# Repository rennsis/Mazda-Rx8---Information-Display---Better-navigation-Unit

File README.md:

In this project i want to share my work for the Mazda RX8 information diplay and the parts that connected to it.

I started the project while working on a "remake" for the navigation unit. Basiclly i want to replace the OEM Navigation unit with an own programmed display where u can see sensors and also troubleshoot your car for example a DTC read out.

Some information in the project i got from already dead github projects. So i will try to continue there work :) Also i alredy want to say thanks to these poeple who was able to help me with there information! 

Currently there wont be much in this Project cause im currently planing on desinging a PCB where everthing will connect. 

| ICON | DATA | ADDRESS |
| ------------- | ------------- | ------------- |
| CD-IN | 0x10 | 0x93 |
| MD-IN | 0x10 | 0x94 |
| L-DIVIDER | 0x10 | 0x91 |
| R-DIVIDER | 0x08 | 0x9B |
| ST | 0x10 | 0x95 |
| DA | 0x01 | 0x95 |
| C° | 0x10 | 0x96 |
| F° | 0x08 | 0x96 |
| TEMP | 0x04 | 0x96 |
| AMB | 0x02 | 0x96 |
| AF | 0x01 | 0x96 |
| CAR | 0x01 | 0x97 |
| PTY | 0x02 | 0x97 |
|  AIR-IN | 0x04 | 0x97 |
| AIR-REUSE | 0x08 | 0x97 |
| AUTO | 0x10 | 0x97 |
| FAN | 0x02 | 0x99 |
| FAN-1 | 0x04 | 0x99 |
| FAN-2 | 0x08 | 0x99 |
| FAN-3 | 0x10 | 0x99 |
| FAN-4 | 0x01 | 0x98 |
| FAN-5 | 0x04 | 0x98 |
| FAN-6 | 0x08 | 0x9D |
| FAN-7 | 0x02 | 0x9B |
| RPT | 0x20 | 0x98 |
| AC | 0x08 | 0x98 |
| ECO | 0x10 | 0x98 |
| AUTO-M | 0x01 | 0x9A |
| TP | 0x02 | 0x9A |
| TA | 0x04 | 0x9A |
| RDM | 0x08 | 0x9A |
| TEXT " | 0x04 | 0x9B |
| TEXT : | 0x10 | 0x9D |
| TEXT-R . | 0x10 | 0x9B |
| PERSON | 0x01 | 0x9C |
| FRONT-HEAT | 0x02 | 0x9C |
| ARROW-FEED | 0x04 | 0x9C |
| ARROW-FACE | 0x04 | 0x9D |
| TMP . | 0x02 | 0x9D |
| CLOCK : | 0x04 | 0x93 |
| CLOCK . | 0x04 | 0x90 |

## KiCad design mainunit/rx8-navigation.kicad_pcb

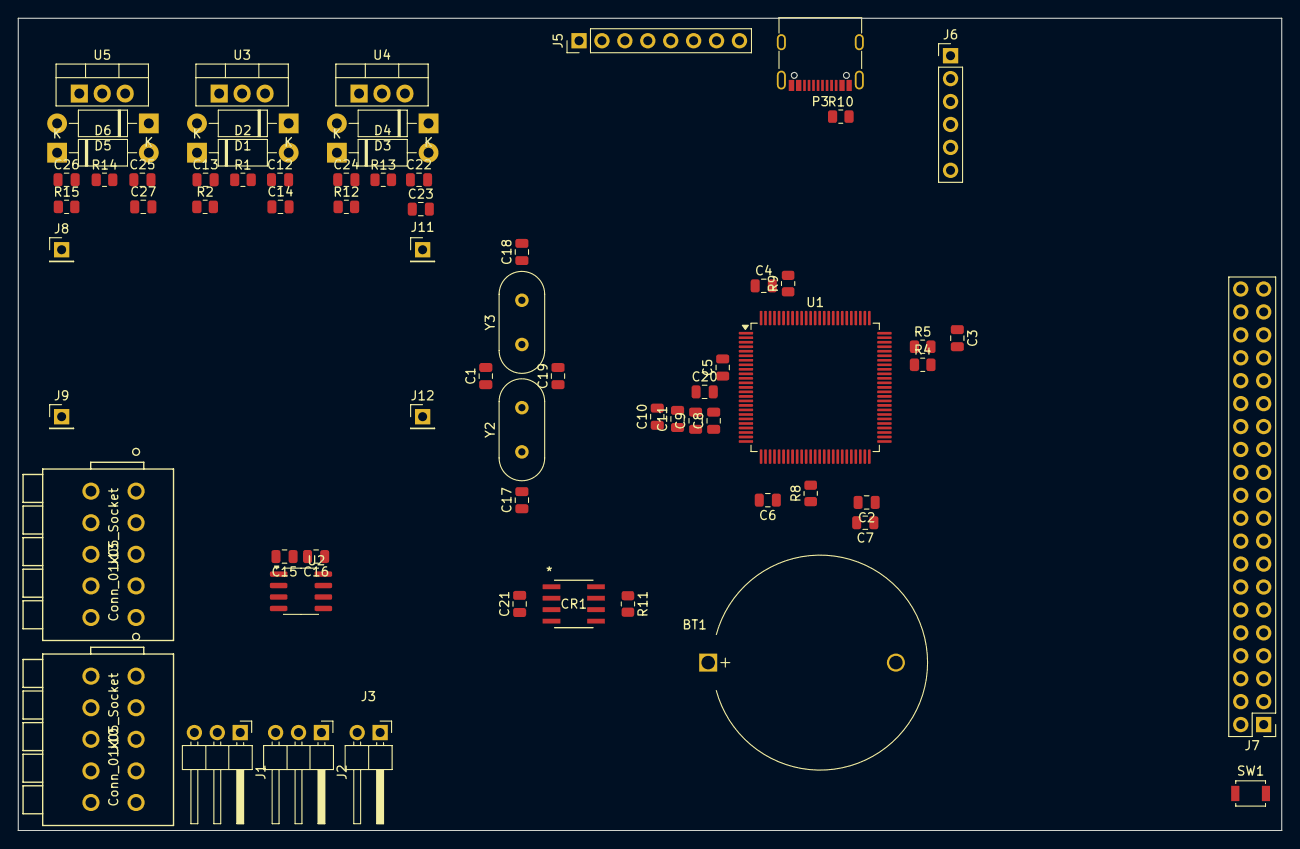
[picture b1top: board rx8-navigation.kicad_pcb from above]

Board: 4 copper layers, 140.0 x 90.0 mm, 68 parts (0 on the bottom side), 62 nets, no tracks yet.

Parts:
BT1: Battery_Cell; BatteryHolder_MYOUNG_BS-07-A1BJ001_CR2032
C1, C17: 10pF; C_SMD
C2, C3, C4, C5, C6, C15, C16, C21: 100nF; C_SMD
C7: 4.7uF; C_SMD
C8, C10: 10nF; C_SMD
C9, C11, C14, C23, C27: 1uF; C_SMD
C12, C20, C22, C25: 0.1uF; C_SMD
C13, C24, C26: 10uF; C_SMD
C18, C19: 20pF; C_SMD
CR1: L9616; SO-8_STM
D1, D2, D3, D4, D5, D6: 1N4001; D_DO-41_SOD81_P10.16mm_Horizontal
J1: BOOT1; PinHeader_1x03_P2.54mm_Horizontal
J2: BOOT0; PinHeader_1x03_P2.54mm_Horizontal
J3: RX/TX; PinHeader_1x02_P2.54mm_Horizontal
J5: MPU-69050; PinHeader_1x08_P2.54mm_Vertical
J6: HC-06; PinHeader_1x06_P2.54mm_Vertical
J7: TFT_Unit; PinHeader_2x20_P2.54mm_Vertical
J8: RegV_IN+; PinHeader_1x01_P2.54mm_Vertical
J9: RegV_IN-; PinHeader_1x01_P2.54mm_Vertical
J10, J13: Conn_01x05_Socket; 2601-1105
J11: RegV_OUT+; PinHeader_1x01_P2.54mm_Vertical
J12: RegV_OUT-; PinHeader_1x01_P2.54mm_Vertical
P3: USB_C_Plug_USB2.0; USB_C_Receptacle_G-Switch_GT-USB-7010ASV
R1, R14: 180; R_SMD
R2, R12, R15: 110; R_SMD
R4, R5: 22; R_SMD
R8, R9: 10k; R_SMD
R10: 5.1k; R_SMD
R11: 120; R_SMD
R13: 330; R_SMD
SW1: RESET; SW_SPST_B3U-1000P
U1: STM32F103VBTx; LQFP-100_14x14mm_P0.5mm
U2: ZXBM5210-S; SOIC-8_3.9x4.9mm_P1.27mm
U3, U4, U5: LM317_TO-220; TO-220-3_Vertical
Y2: 32.768kHz; Crystal_HC18-U_Vertical
Y3: 8MHz; Crystal_HC18-U_Vertical

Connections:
+3.3V: C2.1, C3.1, C4.1, C5.1, C6.1, C7.1, C8.1, C9.1, C10.1, C11.1, C14.1, C15.2, C21.1, C27.1, CR1.3 (VS), D1.2 (A), D2.1 (K), D5.2 (A), D6.1 (K), J1.3, J2.3, J7.29, J10.1, R2.1, R15.1, U1.11 (VDD), U1.21 (VREF+), U1.22 (VDDA), U1.28 (VDD), U1.50 (VDD), U1.75 (VDD), U1.100 (VDD), U2.3 (VDD), U2.6 (VREF), U3.2 (VO), U5.2 (VO)
+5V: C12.1, C23.1, D1.1 (K), D3.2 (A), D4.1 (K), J5.8, J7.5, P3.A4 (VBUS), P3.A9 (VBUS), P3.B4 (VBUS), P3.B9 (VBUS), R12.1, U3.3 (VI), U4.2 (VO)
+12V: C22.1, C25.1, D3.1 (K), D5.1 (K), J11.1, U4.3 (VI), U5.3 (VI)
+BATT: BT1.1 (+), U1.6 (VBAT)
BOOT0: R9.2, U1.94 (BOOT0)
CAN_H: CR1.7 (C_H), J13.7, R11.1
CAN_L: CR1.6 (C_L), J13.9, R11.2
F_CS: J7.9, U1.57 (PD10)
GND: BT1.2 (-), C1.2, C2.2, C3.2, C4.2, C5.2, C6.2, C7.2, C8.2, C9.2, C10.2, C11.2, C12.2, C13.2, C14.2, C15.1, C16.1, C17.1, C18.2, C19.1, C20.1, C21.2, C22.2, C23.2, C24.2, C25.2, C26.2, C27.2, CR1.2 (GND), CR1.8 (ASC), J1.1, J2.1, J5.7, J6.3, J7.39, J9.1, J10.9, J12.1, J13.3, P3.A1 (GND), P3.A12 (GND), P3.B1 (GND), P3.B12 (GND), P3.S1 (SHIELD), R1.2, R10.2, R13.2, R14.2, SW1.2, U1.10 (VSS), U1.19 (VSSA), U1.20 (VREF-), U1.27 (VSS), U1.49 (VSS), U1.74 (VSS), U1.99 (VSS), U2.8 (GND)
HC_RXD: J6.5, U1.25 (PA2)
HC_TXD: J6.4, U1.26 (PA3)
I2C_SCL: J5.6, U1.92 (PB6)
I2C_SDA: J5.5, U1.93 (PB7)
MOTOR_B: U1.79 (PC11), U2.5 (REV)
MOTOR_GND: J10.7, U2.1 (OUT1)
MOTOR_POS: J10.3, U1.80 (PC12)
MOTOR_VDD: J10.5, U2.7 (OUT2)
NRST: C20.2, SW1.1, U1.14 (NRST)
unnamed: C13.1, D2.2 (A), R1.1, R2.2, U3.1 (ADJ)
unnamed: C24.1, D4.2 (A), R12.2, R13.1, U4.1 (ADJ)
unnamed: C26.1, D6.2 (A), R14.1, R15.2, U5.1 (ADJ)
unnamed: J1.2, R8.1
unnamed: J2.2, R9.1
unnamed: P3.A5 (CC), R10.1
unnamed: R4.1, U1.70 (PA11)
unnamed: R5.1, U1.71 (PA12)
unnamed: C16.2, U2.2 (VM)
OSC_IN: C18.1, U1.12 (OSC_IN), Y3.2
OSC_OUT: C19.2, U1.13 (OSC_OUT), Y3.1
PB_2 / BOOT1: R8.2, U1.37 (PB2)
PC14: C1.1, U1.8 (PC14), Y2.2
PC15: C17.2, U1.9 (PC15), Y2.1
RX / PA10: J3.2, U1.69 (PA10)
SD_CS: J7.6, U1.58 (PD11)
SPI_MISO: J7.12, J7.16, U1.31 (PA6)
SPI_MOSI: J7.4, J7.8, J7.20, U1.32 (PA7)
SPI_SCK: J7.2, J7.10, J7.24, U1.30 (PA5)
TFT_CS: J7.11, U1.55 (PD8)
TFT_DB0: J7.40, U1.88 (PD7)
TFT_DB1: J7.38, U1.87 (PD6)
TFT_DB2: J7.36, U1.86 (PD5)
TFT_DB3: J7.34, U1.85 (PD4)
TFT_DB4: J7.32, U1.84 (PD3)
TFT_DB5: J7.30, U1.82 (PD1)
TFT_DB6: J7.28, U1.81 (PD0)
TFT_DB7: J7.26, U1.46 (PE15)
TFT_DB8: J7.27, U1.45 (PE14)
TFT_DB9: J7.25, U1.44 (PE13)
TFT_DB10: J7.23, U1.43 (PE12)
TFT_DB11: J7.21, U1.42 (PE11)
TFT_DB12: J7.19, U1.41 (PE10)
TFT_DB13: J7.17, U1.40 (PE9)
TFT_DB14: J7.15, U1.39 (PE8)
TFT_DB15: J7.13, U1.38 (PE7)
TFT_RESET: J7.7, U1.62 (PD15)
TFT_RS: J7.33, U1.60 (PD13)
TFT_WR: J7.31, U1.61 (PD14)
TX / PA9: J3.1, U1.68 (PA9)
T_CS: J7.22, U1.59 (PD12)
USB_D+: P3.A6 (D+), R5.2
USB_D-: P3.A7 (D-), R4.2
VDD: J8.1, J13.1

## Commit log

2024-12-18 Added AC Connector Image
2024-12-18 Added PCB Schematic and PCB
2024-12-23 Update README.md
    Added icon addresses with data

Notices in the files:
parts and their libraries:
Copyright 2016 Accelerated Designs. All rights reserved.
